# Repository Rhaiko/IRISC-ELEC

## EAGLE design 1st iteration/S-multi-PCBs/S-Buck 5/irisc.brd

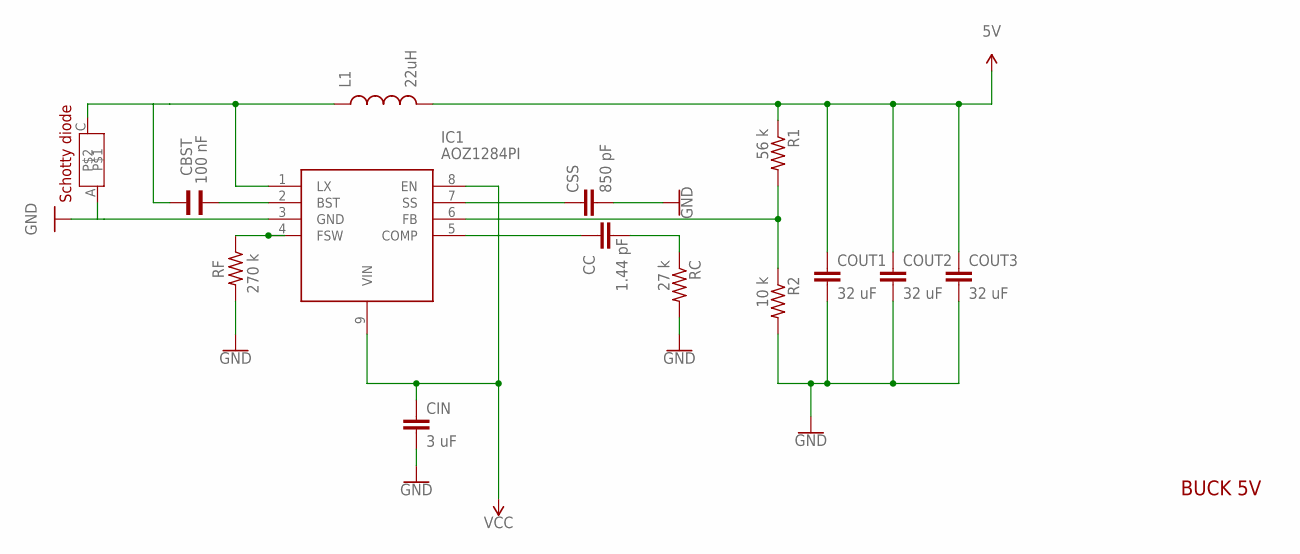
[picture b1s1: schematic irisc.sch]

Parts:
CBST: 100 nF; WCAP-CSGP_0805_WAVE
CC: 1.44 pF; C1206
CIN: 3 uF; C1210
COUT1, COUT2, COUT3: 32 uF; C1812
CSS: 850 pF; C0805
IC1: AOZ1284PI; SOIC127P600X170-9N
L1: 22uH; L0603
R1: 56 k; 0805-THM
R2: 10 k; 0805-THM
RC: 27 k; 0805-THM
RF: 270 k; 0805-THM
U$1: SCHOTTY-DIODE-IRISC; DO-214AC

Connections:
5V: COUT1.1, COUT2.1, COUT3.1, L1.2, R1.1
GND: CIN.2, COUT1.2, COUT2.2, COUT3.2, CSS.2, IC1.3 (GND), R2.2, RC.2, RF.2, U$1.A
unnamed: CSS.1, IC1.7 (SS)
unnamed: IC1.4 (FSW), RF.1
unnamed: CBST.2, IC1.2 (BST)
unnamed: CBST.1, IC1.1 (LX), L1.1, U$1.C
unnamed: CC.1, IC1.5 (COMP)
unnamed: IC1.6 (FB), R1.2, R2.1
unnamed: CC.2, RC.1
VCC: CIN.1, IC1.8 (EN), IC1.9 (VIN)

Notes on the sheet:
BUCK 5V

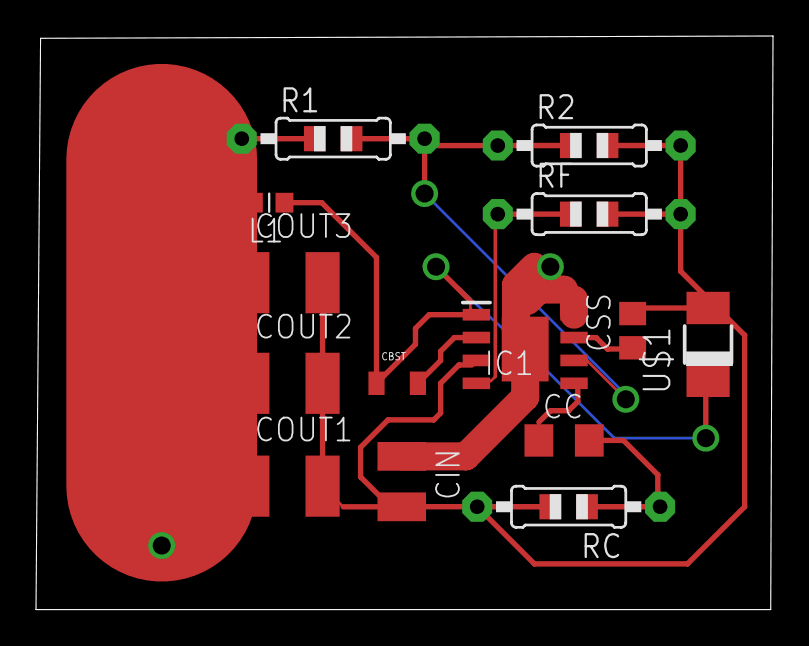
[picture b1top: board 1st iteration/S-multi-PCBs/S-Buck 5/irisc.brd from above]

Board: 2 copper layers, 40.9 x 31.9 mm, 14 parts (0 on the bottom side), 10 nets.

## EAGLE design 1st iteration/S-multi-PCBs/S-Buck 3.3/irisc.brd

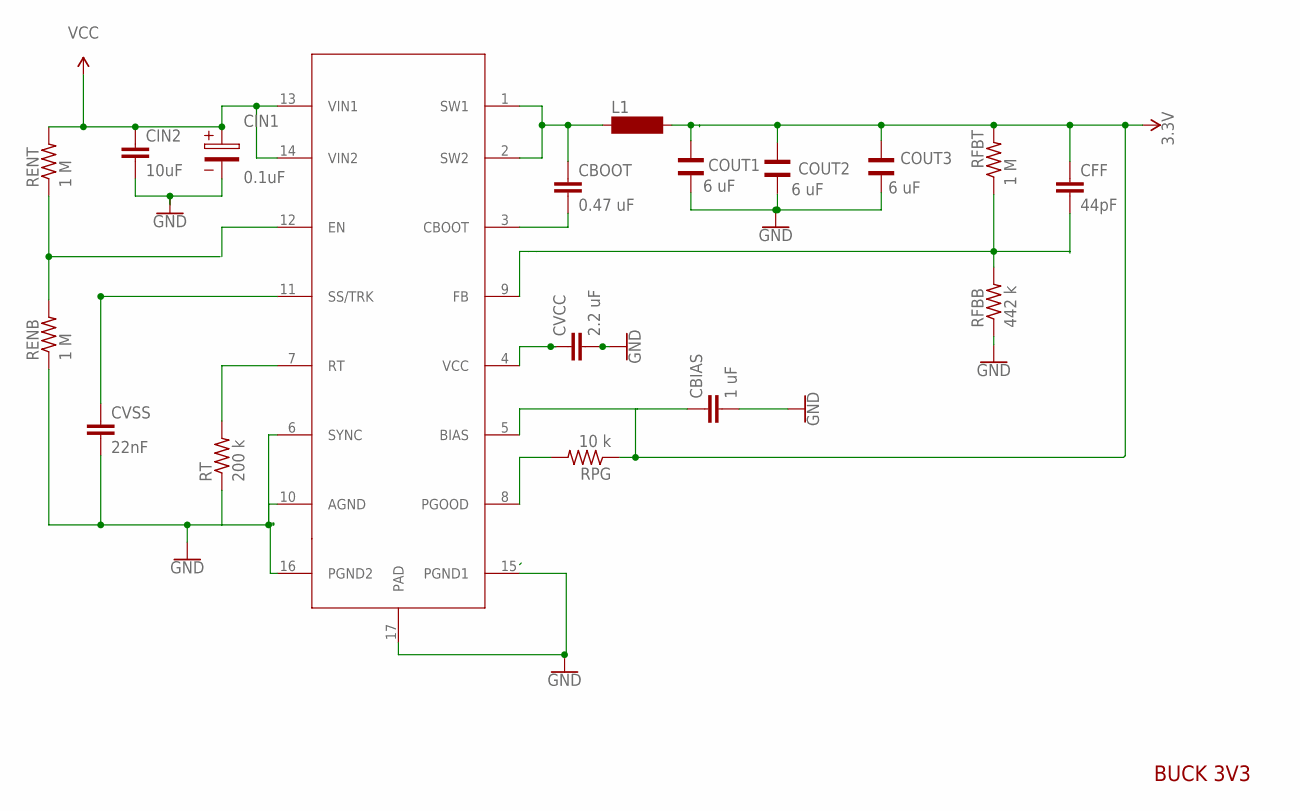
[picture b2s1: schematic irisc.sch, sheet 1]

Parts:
BUCK3V1: BUCK3V3; SOP65P640X120-17N
CBIAS: 1 uF; C1210
CBOOT: 0.47 uF; C1210
CFF: 44pF; C0603
CIN1: 0.1uF; 6.3X2.5X0.9(DXAXB)
CIN2: 10uF; C0805
COUT1, COUT2, COUT3: 6 uF; WCAP-CSGP_0805_WAVE
CVCC: 2.2 uF; C1210
CVSS: 22nF; C1206
L1: BS11
RENB: 1 M; 0805-THM
RENT: 1 M; 0805-THM
RFBB: 442 k; 0805-THM
RFBT: 1 M; 0805-THM
RPG: 10 k; 0805-THM
RT: 200 k; 0805-THM

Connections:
3.3V: BUCK3V1.5 (BIAS), CBIAS.1, CFF.1, COUT1.2, COUT2.2, COUT3.2, L1.2, RFBT.2, RPG.1
GND: CBIAS.2, CIN1.2, CIN2.2, COUT1.1, COUT2.1, COUT3.1, CVCC.2, RFBB.1; also elsewhere on the board
unnamed: BUCK3V1.1 (SW1), BUCK3V1.2 (SW2), CBOOT.1, L1.1
unnamed: BUCK3V1.7 (RT), RT.2
unnamed: BUCK3V1.11 (SS/TRK), CVSS.1
unnamed: BUCK3V1.3 (CBOOT), CBOOT.2
unnamed: CFF.2, RFBB.2, RFBT.1
unnamed: BUCK3V1.4 (VCC), CVCC.1
unnamed: BUCK3V1.8 (PGOOD), RPG.2
unnamed: RENB.2, RENT.1
PGND1: BUCK3V1.15 (PGND1), BUCK3V1.17 (PAD)
PGND2: BUCK3V1.6 (SYNC), BUCK3V1.10 (AGND), BUCK3V1.16 (PGND2), CVSS.2, RENB.1, RT.1
VCC1: BUCK3V1.13 (VIN1), BUCK3V1.14 (VIN2), CIN1.1, CIN2.1, RENT.2

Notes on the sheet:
BUCK 3V3

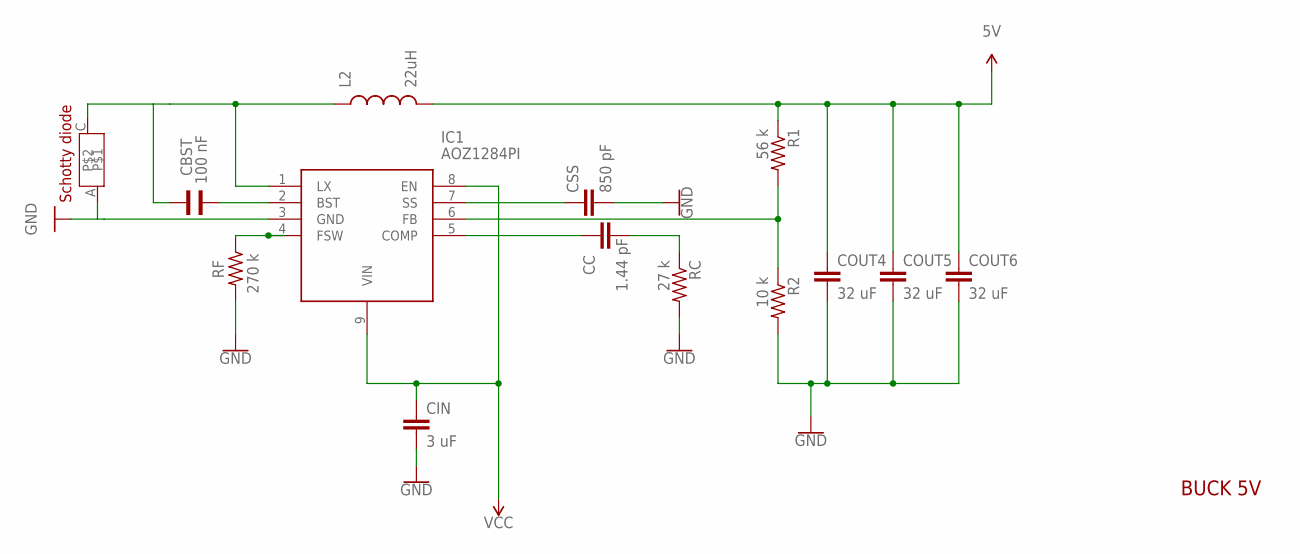
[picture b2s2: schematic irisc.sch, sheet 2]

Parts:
CBST: 100 nF; WCAP-CSGP_0805_WAVE
CC: 1.44 pF; C1206
CIN: 3 uF; C1210
COUT4, COUT5, COUT6: 32 uF; C1812
CSS: 850 pF; C0805
IC1: AOZ1284PI; SOIC127P600X170-9N
L2: 22uH; L0603
R1: 56 k; 0805-THM
R2: 10 k; 0805-THM
RC: 27 k; 0805-THM
RF: 270 k; 0805-THM
U$1: SCHOTTY-DIODE-IRISC; DO-214AC

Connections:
5V: COUT4.1, COUT5.1, COUT6.1, L2.2, R1.1
GND: CIN.2, COUT4.2, COUT5.2, COUT6.2, CSS.2, IC1.3 (GND), R2.2, RC.2, RF.2, U$1.A; also elsewhere on the board
unnamed: IC1.4 (FSW), RF.1
unnamed: CBST.2, IC1.2 (BST)
unnamed: CBST.1, IC1.1 (LX), L2.1, U$1.C
unnamed: CC.1, IC1.5 (COMP)
unnamed: CSS.1, IC1.7 (SS)
unnamed: IC1.6 (FB), R1.2, R2.1
unnamed: CC.2, RC.1
VCC: CIN.1, IC1.8 (EN), IC1.9 (VIN)

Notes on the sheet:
BUCK 5V

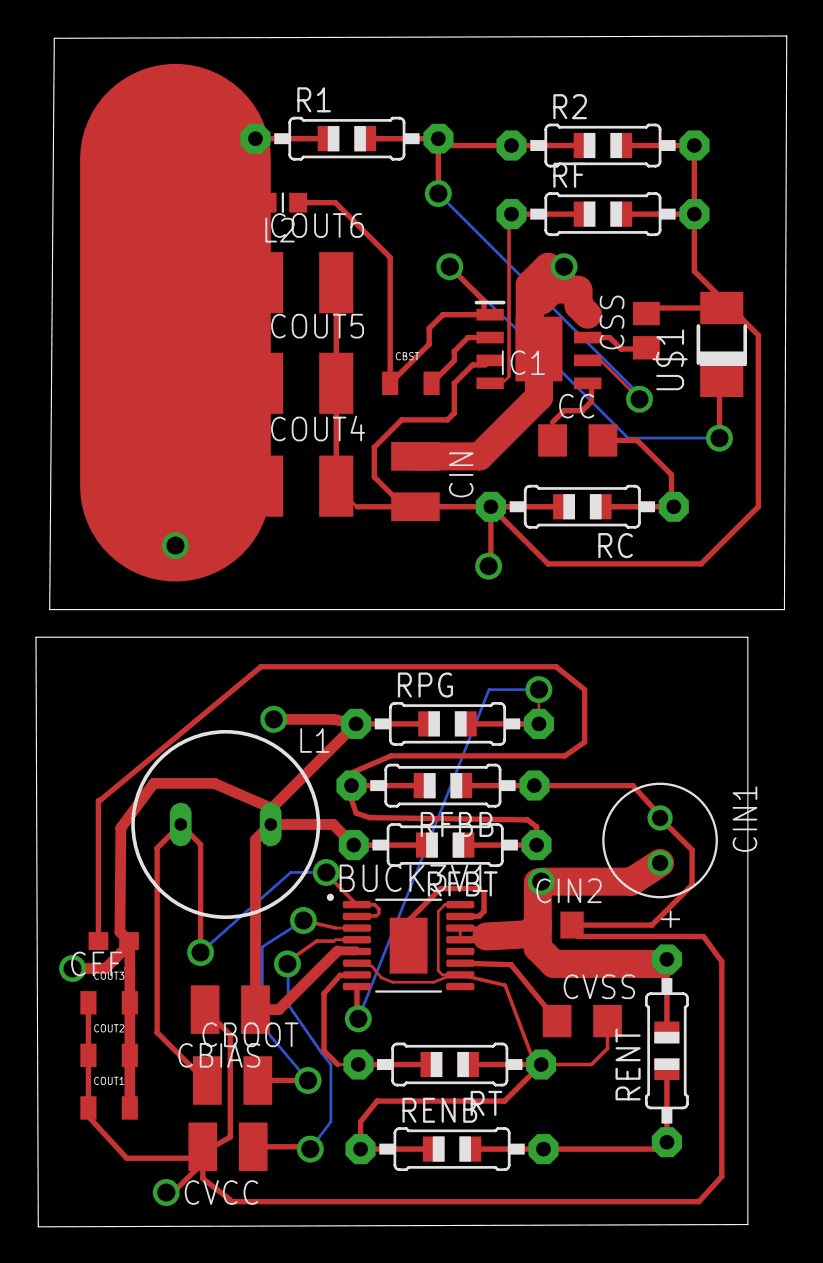
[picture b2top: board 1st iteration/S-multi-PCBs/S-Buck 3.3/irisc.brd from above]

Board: 2 copper layers, 41.7 x 66.2 mm, 32 parts (0 on the bottom side), 22 nets.

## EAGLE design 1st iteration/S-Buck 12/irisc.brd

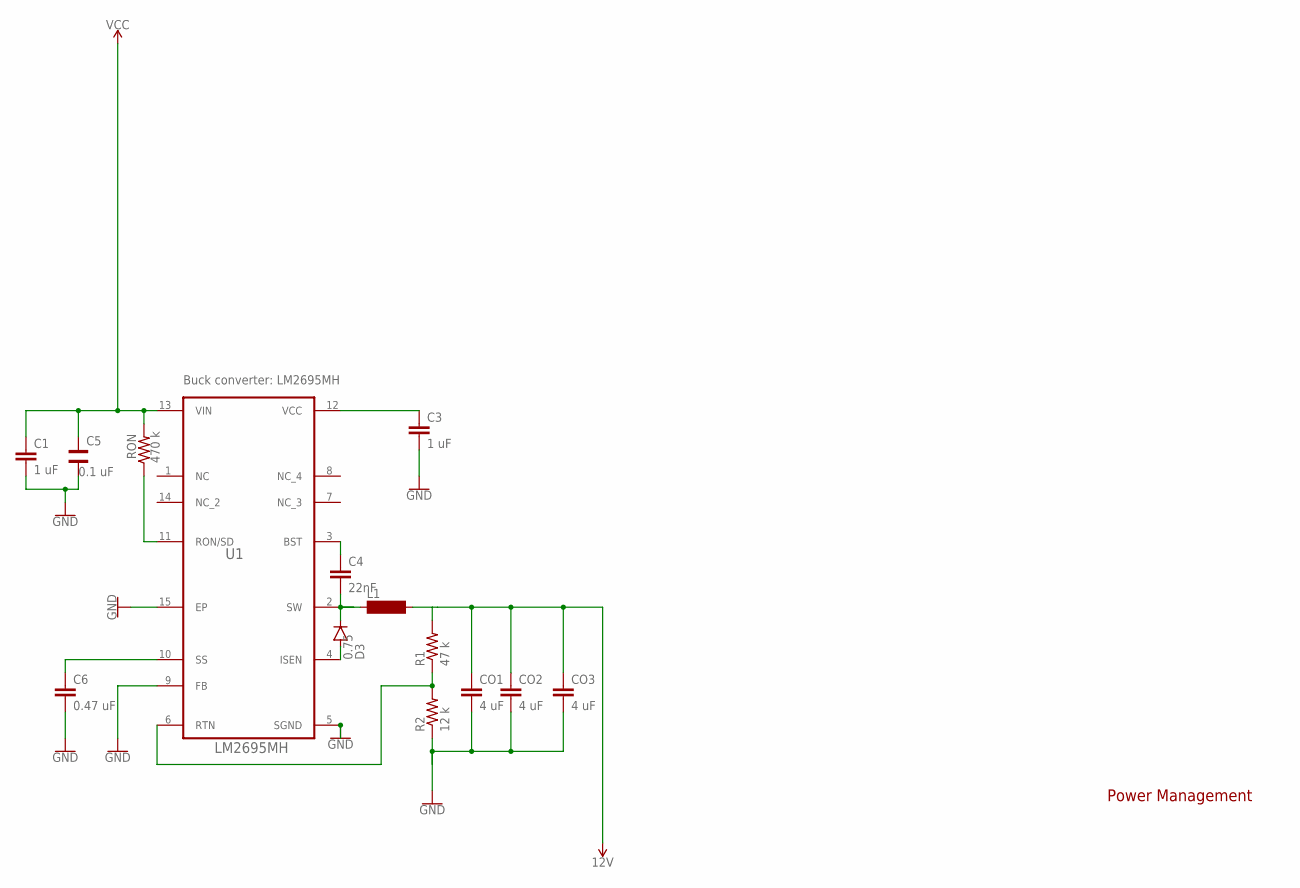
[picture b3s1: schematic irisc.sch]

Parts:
C1, C3: 1 uF; C1210
C4: 22nF; C1206
C5: 0.1 uF; WCAP-CSGP_0805_REFLOW
C6: 0.47 uF; C1210
CO1, CO2, CO3: 4 uF; C1812
D3: 0.75; DIODE-1N4001-KIT
L1: BS11
R1: 47 k; 0805-THM
R2: 12 k; 0805-THM
RON: 470 k; 0805-THM
U1: LM2695MH; SOP65P640X110-15N

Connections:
12V: CO1.1, CO2.1, CO3.1, L1.2, R1.2
GND: C1.2, C3.2, C5.1, C6.2, CO1.2, CO2.2, CO3.2, R2.1, U1.5 (SGND), U1.9 (FB), U1.15 (EP)
unnamed: R1.1, R2.2, U1.6 (RTN)
unnamed: C3.1, U1.12 (VCC)
unnamed: C4.1, U1.3 (BST)
unnamed: C4.2, D3.C, L1.1, U1.2 (SW)
unnamed: RON.1, U1.11 (RON/SD)
unnamed: C6.1, U1.10 (SS)
unnamed: D3.A, U1.4 (ISEN)
VCC: C1.1, C5.2, RON.2, U1.13 (VIN)

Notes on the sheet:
Buck converter: LM2695MH
Power Management

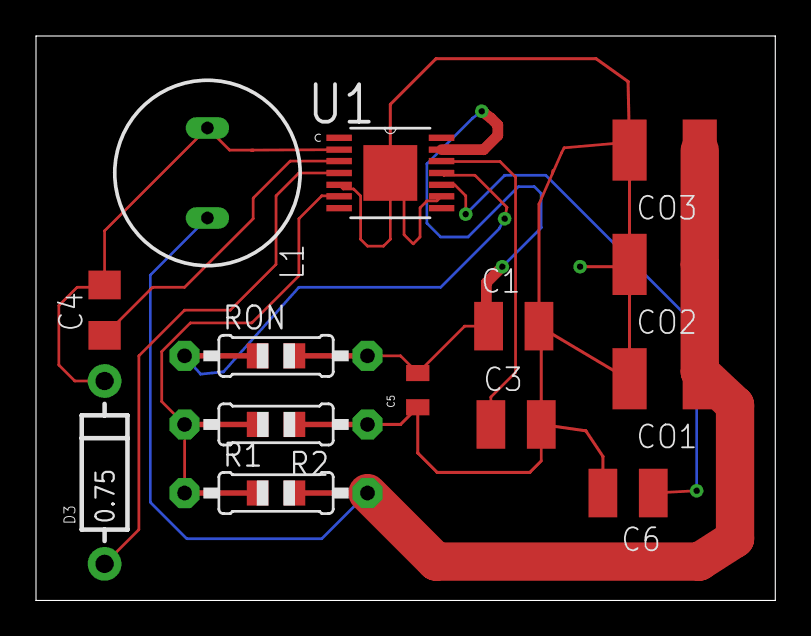
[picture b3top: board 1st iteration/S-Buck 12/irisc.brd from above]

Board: 2 copper layers, 41.1 x 31.4 mm, 14 parts (0 on the bottom side), 10 nets.

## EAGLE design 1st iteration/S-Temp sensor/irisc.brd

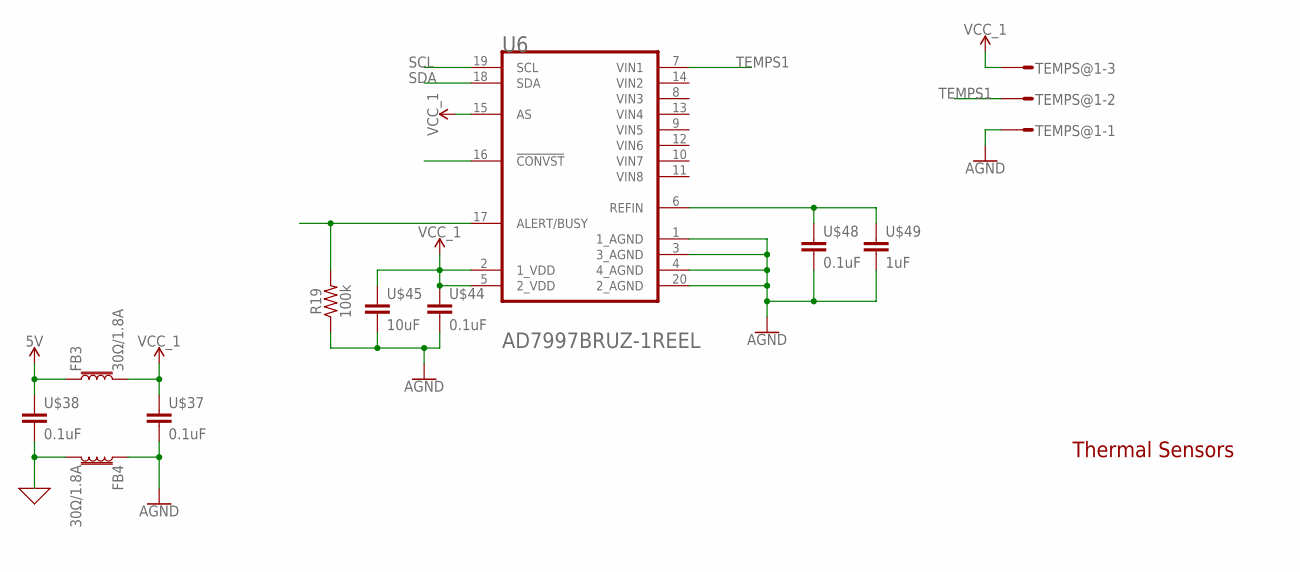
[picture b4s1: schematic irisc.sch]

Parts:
FB3, FB4: 30Ω/1.8A; 0603
R19: 100k; 0603
TEMPS@1: L03P
U6: ANALOG_DEVICES_AD7997BRUZ-1REELANALOG_DEVICES_AD7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; ANALOG_DEVICES_AD7997BRUZ-1REEL_0
U$37, U$38, U$44, U$48: 0.1uF; RESC0603_N
U$45: 10uF; RESC0805_L
U$49: 1uF; RESC0603_N

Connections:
0: FB4.2, U$38.2
5V: FB3.1, U$38.1
AGND: FB4.1, R19.1, TEMPS@1.1, U6.1 (1_AGND), U6.3 (3_AGND), U6.4 (4_AGND), U6.20 (2_AGND), U$37.2, U$44.2, U$45.2, U$48.2, U$49.2
unnamed: U6.6 (REFIN), U$48.1, U$49.1
unnamed: R19.2, U6.17 (ALERT/BUSY)
SCL: U6.19 (SCL)
SDA: U6.18 (SDA)
TEMPS1: TEMPS@1.2, U6.7 (VIN1)
VCC_1: FB3.2, TEMPS@1.3, U6.2 (1_VDD), U6.5 (2_VDD), U6.15 (AS), U$37.1, U$44.1, U$45.1

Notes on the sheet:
Thermal Sensors

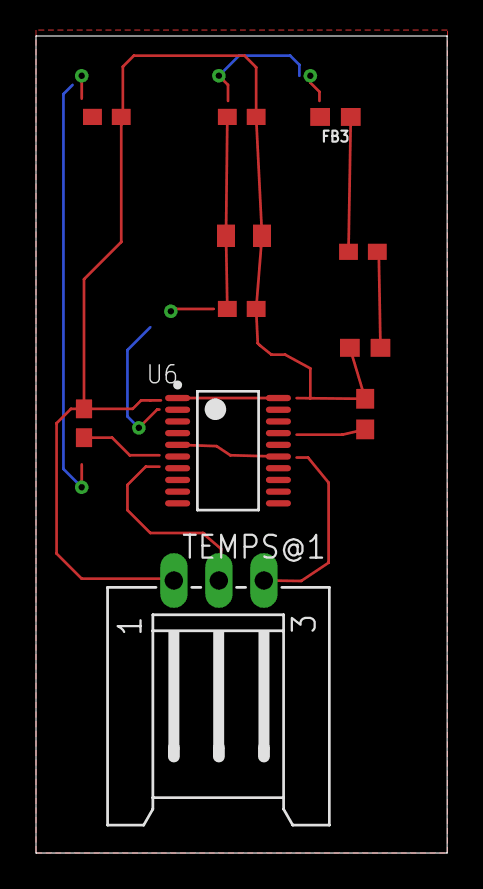
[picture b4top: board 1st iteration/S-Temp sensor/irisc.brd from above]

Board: 2 copper layers, 22.8 x 45.4 mm, 11 parts (0 on the bottom side), 7 nets.

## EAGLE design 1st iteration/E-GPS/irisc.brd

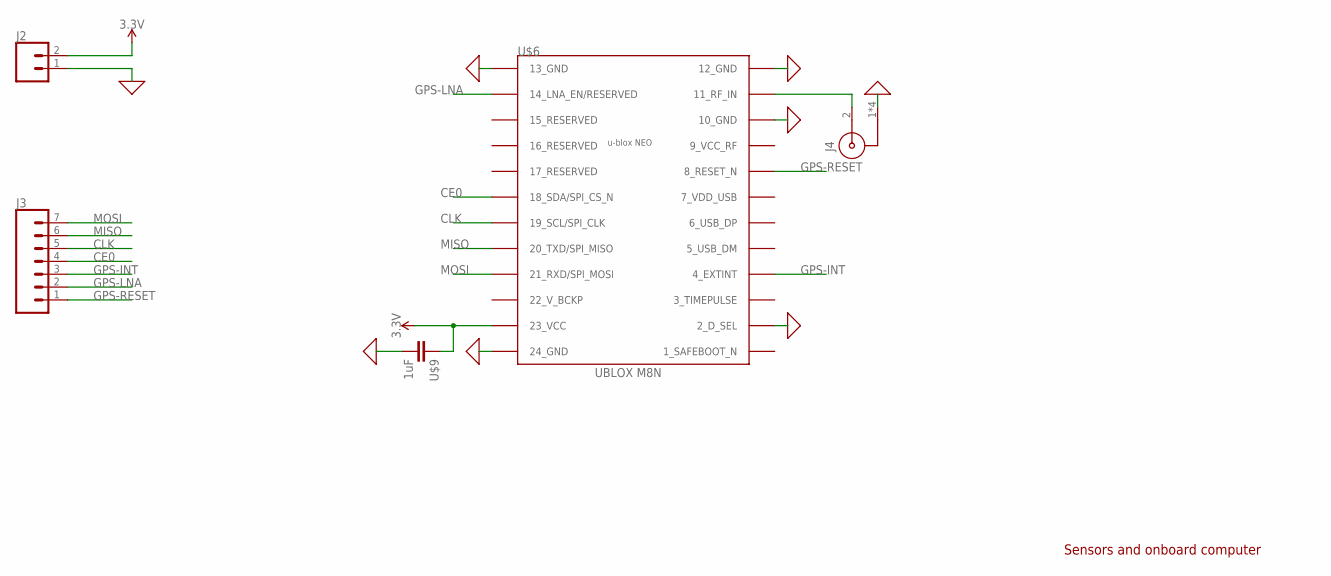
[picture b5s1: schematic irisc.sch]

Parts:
J2: CONN_02; 1X02
J3: CONN_07; 1X07
J4: 60312202114508
U$6: NEO-M8
U$9: 1uF; RESC0603_N

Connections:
0: J2.1, J4.1 (2), J4.3 (2), J4.4 (2), J4.5 (2), U$6.2 (2_D_SEL), U$6.10 (10_GND), U$6.12 (12_GND), U$6.13 (13_GND), U$6.24 (24_GND), U$9.2
3.3V: J2.2, U$6.23 (23_VCC), U$9.1
CE0: J3.4, U$6.18 (18_SDA/SPI_CS_N)
CLK: J3.5, U$6.19 (19_SCL/SPI_CLK)
GPS-INT: J3.3, U$6.4 (4_EXTINT)
GPS-LNA: J3.2, U$6.14 (14_LNA_EN/RESERVED)
GPS-RESET: J3.1, U$6.8 (8_RESET_N)
MISO: J3.6, U$6.20 (20_TXD/SPI_MISO)
MOSI: J3.7, U$6.21 (21_RXD/SPI_MOSI)
unnamed: J4.2 (1), U$6.11 (11_RF_IN)

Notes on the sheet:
Sensors and onboard computer

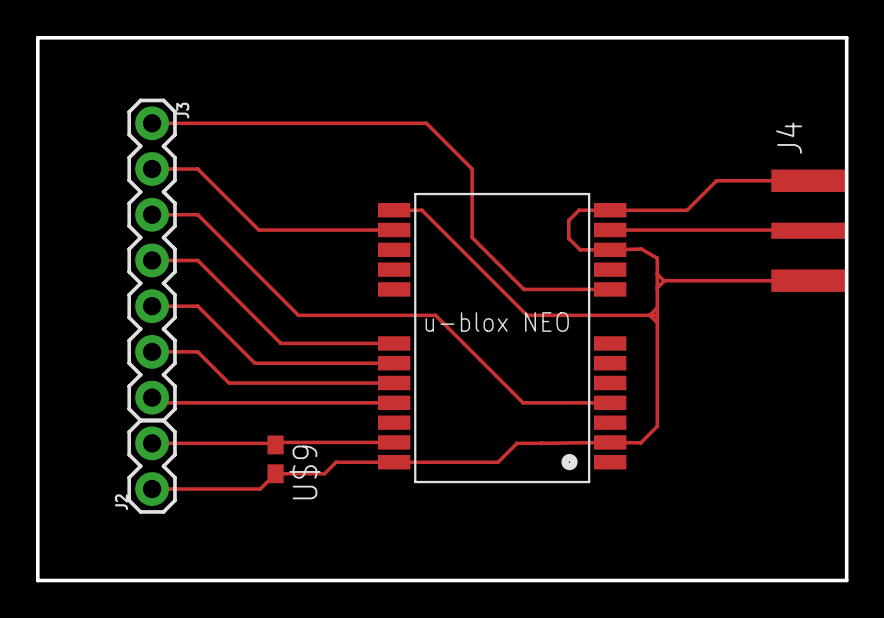
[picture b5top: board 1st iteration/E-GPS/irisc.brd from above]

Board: 2 copper layers, 44.9 x 30.1 mm, 5 parts (0 on the bottom side), 10 nets.

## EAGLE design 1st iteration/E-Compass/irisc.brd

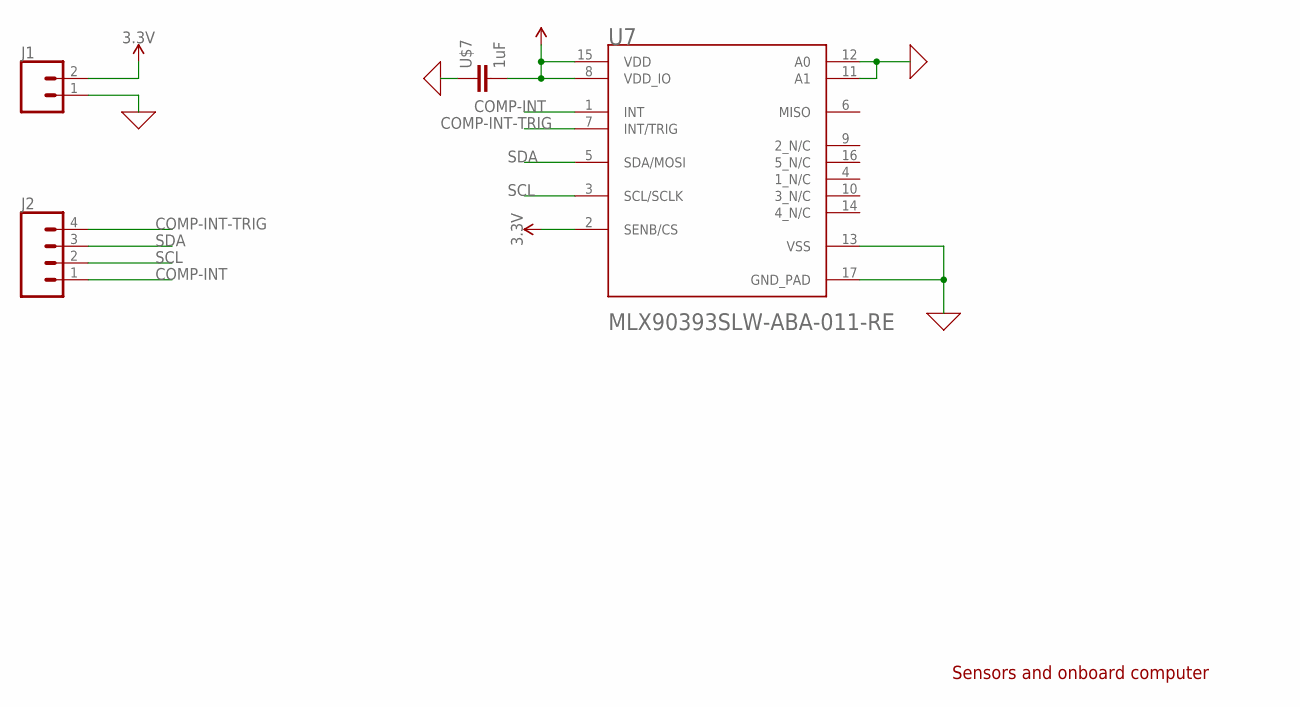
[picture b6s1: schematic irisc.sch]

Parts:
J1: CONN_02; 1X02
J2: CONN_04; 1X04
U7: MELEXIS_TECHNOLOGIES_MLX90393SLW-ABA-011-REMELEXI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; MELEXIS_TECHNOLOGIES_MLX90393SLW-ABA-011-RE_0
U$7: 1uF; RESC0603_N

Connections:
0: J1.1, U7.11 (A1), U7.12 (A0), U7.13 (VSS), U7.17 (GND_PAD), U$7.1
3.3V: J1.2, U7.2 (SENB/CS), U7.8 (VDD_IO), U7.15 (VDD), U$7.2
COMP-INT: J2.1, U7.1 (INT)
COMP-INT-TRIG: J2.4, U7.7 (INT/TRIG)
SCL: J2.2, U7.3 (SCL/SCLK)
SDA: J2.3, U7.5 (SDA/MOSI)

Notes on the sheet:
Sensors and onboard computer

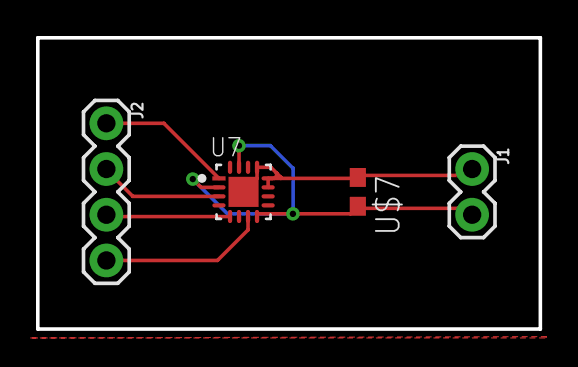
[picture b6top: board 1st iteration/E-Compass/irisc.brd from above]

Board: 2 copper layers, 27.9 x 16.2 mm, 4 parts (0 on the bottom side), 6 nets.

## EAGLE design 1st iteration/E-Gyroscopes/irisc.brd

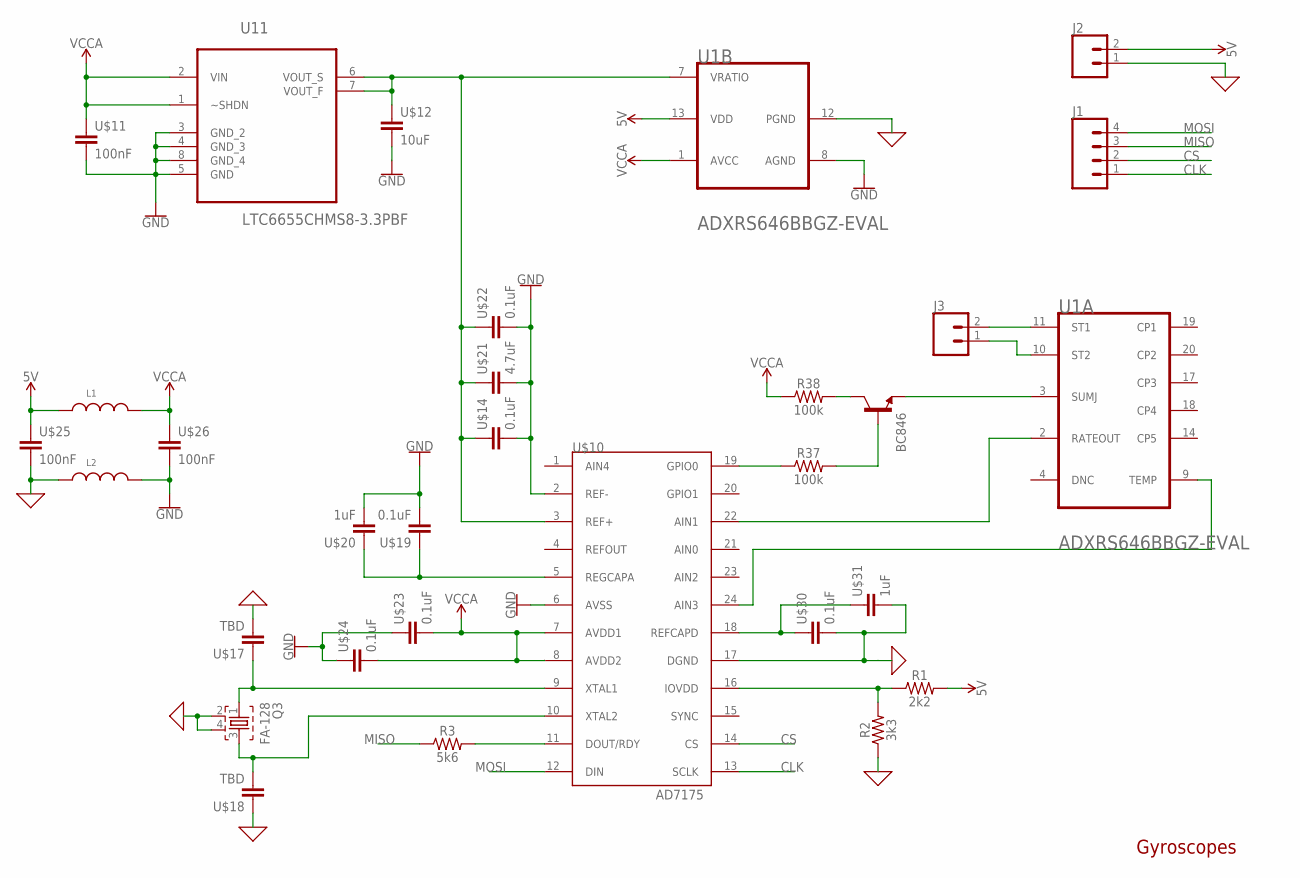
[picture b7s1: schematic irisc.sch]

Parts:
J1: CONN_04; 1X04
J2, J3: CONN_02; 1X02
L1, L2: WE-CBA_0805_782853152_HC; WE-CBA_0805(W=4)
Q3: FA-128
R1: 2k2; AXIAL-0.3-KIT
R2: 3k3; AXIAL-0.3-KIT
R3: 5k6; AXIAL-0.3-KIT
R37, R38: 100k; AXIAL-0.3-KIT
T1: BC846; SOT23
U1: ANALOG_DEVICES_ADXRS646BBGZEVAL; HDRVR20W64P762X254_2X10_2540X1016X254B
U11: LTC6655CHMS8-3.3PBF; SOP65P490X110-8N
U$10: AD7175; TSSOP24
U$11, U$25, U$26: 100nF; RESC0603_N
U$12: 10uF; RESC0805_L
U$14, U$19, U$22, U$23, U$24, U$30: 0.1uF; RESC0603_N
U$17, U$18: TBD; RESC0805_L
U$20, U$31: 1uF; RESC0603_N
U$21: 4.7uF; RESC0603_N

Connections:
0: J2.1, L2.1, Q3.2, Q3.4, R2.P$1 (1), U1.12 (PGND), U$10.17 (DGND), U$17.2, U$18.1, U$25.2, U$30.2, U$31.2
5V: J2.2, L1.1, R1.P$2 (2), U1.13 (VDD), U$25.1
CLK: J1.1, U$10.13 (SCLK)
CP5: U1.14 (CP5)
CS: J1.2, U$10.14 (CS)
GND: L2.2, U1.8 (AGND), U11.3 (GND_2), U11.4 (GND_3), U11.5 (GND), U11.8 (GND_4), U$10.2 (REF-), U$10.6 (AVSS), U$11.2, U$12.2, U$14.2, U$19.2, U$20.2, U$21.2, U$22.2, U$23.1, U$24.1, U$26.2
MISO: J1.3, R3.P$1 (1)
MOSI: J1.4, U$10.12 (DIN)
unnamed: J3.1, U1.10 (ST2)
unnamed: Q3.3, U$10.10 (XTAL2), U$18.2
unnamed: Q3.1, U$10.9 (XTAL1), U$17.1
unnamed: J3.2, U1.11 (ST1)
unnamed: R38.P$2 (2), T1.3 (C)
unnamed: U$10.5 (REGCAPA), U$19.1, U$20.1
unnamed: R37.P$2 (2), T1.1 (B)
unnamed: U1.7 (VRATIO), U11.6 (VOUT_S), U11.7 (VOUT_F), U$10.3 (REF+), U$12.1, U$14.1, U$21.1, U$22.1
unnamed: R1.P$1 (1), R2.P$2 (2), U$10.16 (IOVDD)
unnamed: U$10.18 (REFCAPD), U$30.1, U$31.1
unnamed: T1.2 (E), U1.3 (SUMJ)
unnamed: U1.2 (RATEOUT), U$10.22 (AIN1)
unnamed: U1.9 (TEMP), U$10.24 (AIN3)
unnamed: R37.P$1 (1), U$10.19 (GPIO0)
SDF: R3.P$2 (2), U$10.11 (DOUT/RDY)
VCCA: L1.2, R38.P$1 (1), U1.1 (AVCC), U11.1 (~SHDN), U11.2 (VIN), U$10.7 (AVDD1), U$10.8 (AVDD2), U$11.1, U$23.2, U$24.2, U$26.1

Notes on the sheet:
Gyroscopes

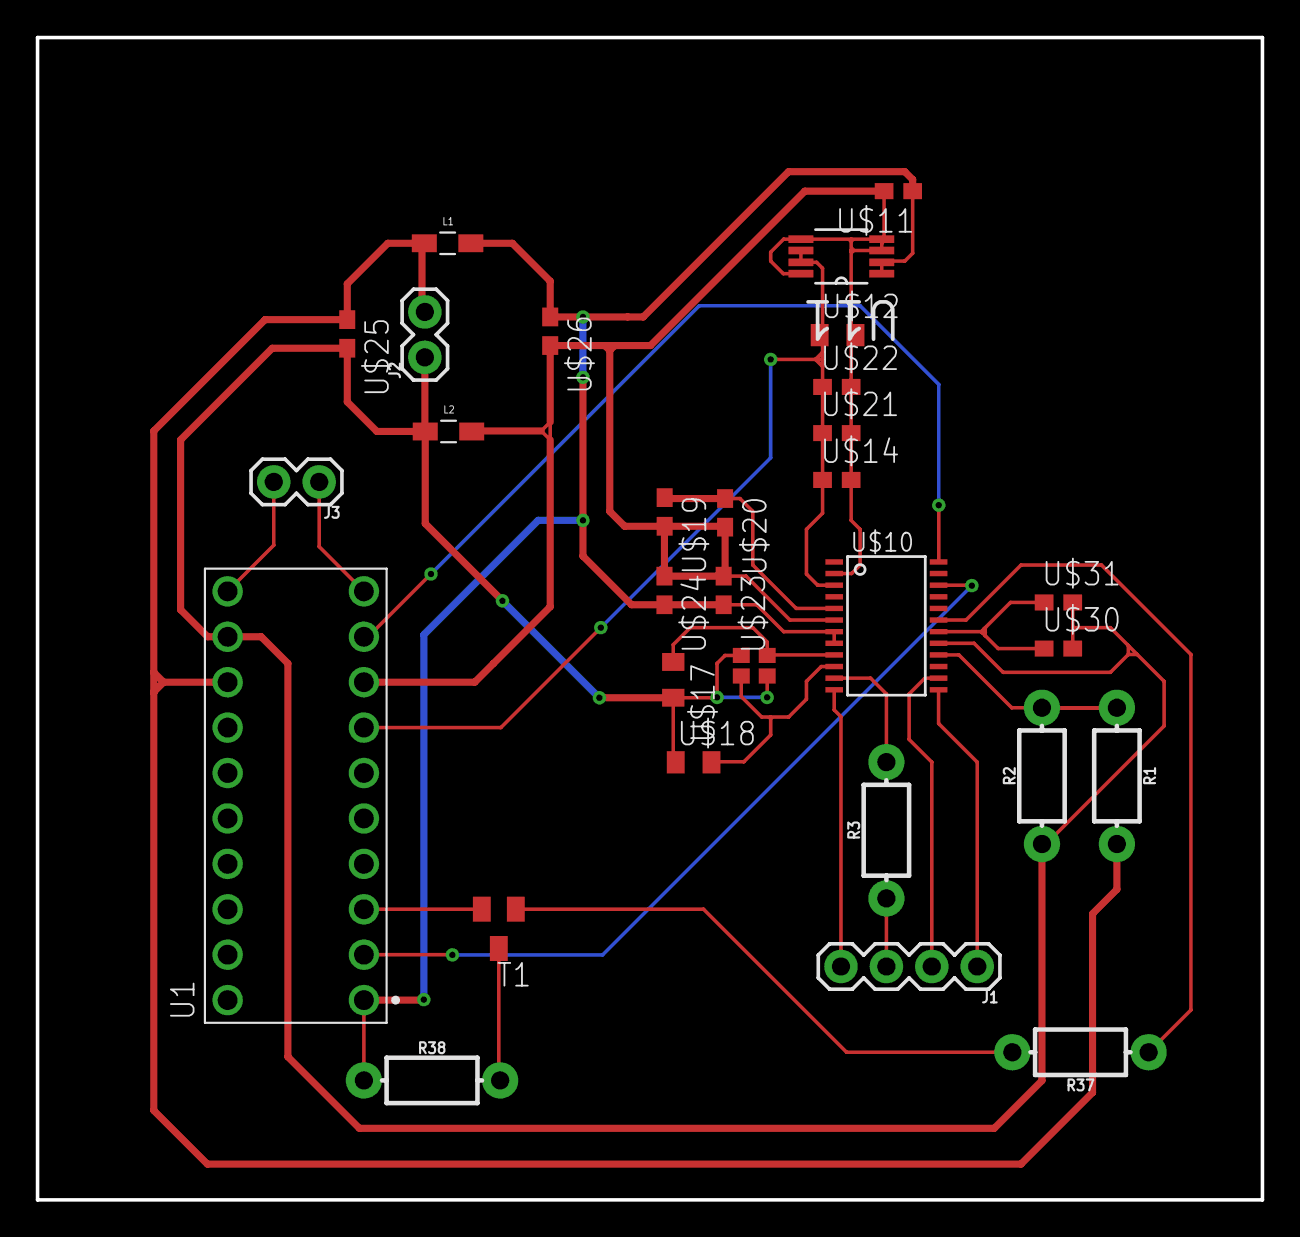
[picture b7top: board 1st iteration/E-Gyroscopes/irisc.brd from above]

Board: 2 copper layers, 68.5 x 65.0 mm, 30 parts (0 on the bottom side), 23 nets.

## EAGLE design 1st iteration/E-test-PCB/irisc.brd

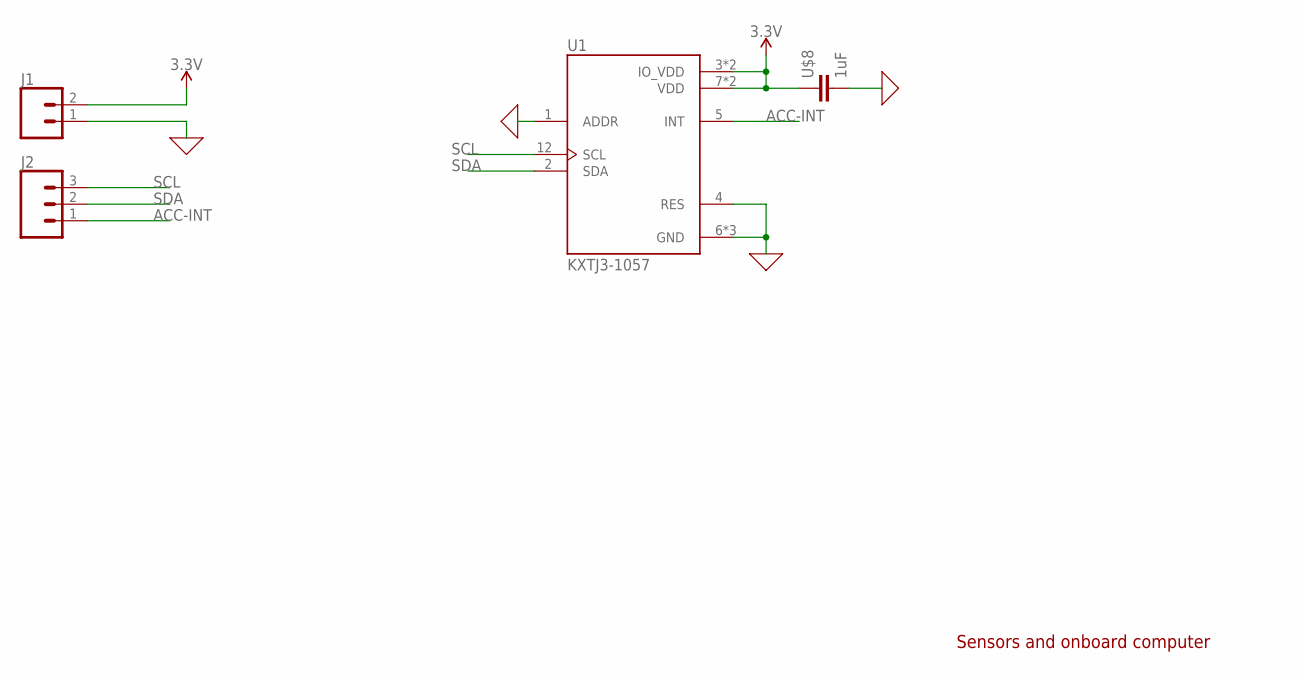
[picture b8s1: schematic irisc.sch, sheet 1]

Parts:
J1: CONN_02; 1X02
J2: CONN_03; 1X03
U1: KXTJ3-1057; KIONIX_KXTJ3-1057
U$8: 1uF; RESC0603_N

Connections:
0: J1.1, U1.1 (ADDR), U1.4 (RES), U1.6 (GND), U1.8 (GND), U1.9 (GND), U$8.2; also elsewhere on the board
3.3V: J1.2, U1.3 (IO_VDD), U1.7 (VDD), U1.10 (VDD), U1.11 (IO_VDD), U$8.1; also elsewhere on the board
ACC-INT: J2.1, U1.5 (INT)
SCL: J2.3, U1.12 (SCL); also elsewhere on the board
SDA: J2.2, U1.2 (SDA); also elsewhere on the board

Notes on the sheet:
Sensors and onboard computer

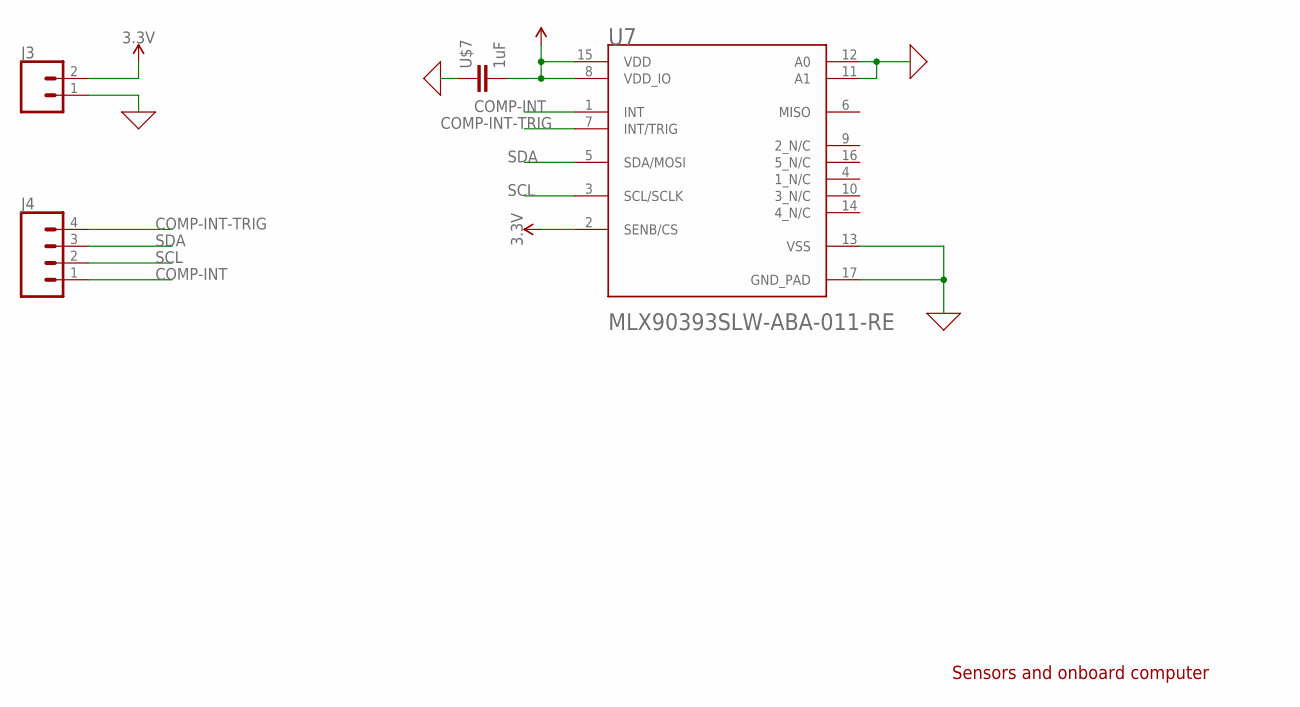
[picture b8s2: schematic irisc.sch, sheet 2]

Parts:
J3: CONN_02; 1X02
J4: CONN_04; 1X04
U7: MELEXIS_TECHNOLOGIES_MLX90393SLW-ABA-011-REMELEXI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; MELEXIS_TECHNOLOGIES_MLX90393SLW-ABA-011-RE_0
U$7: 1uF; RESC0603_N

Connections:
0: J3.1, U7.11 (A1), U7.12 (A0), U7.13 (VSS), U7.17 (GND_PAD), U$7.1; also elsewhere on the board
3.3V: J3.2, U7.2 (SENB/CS), U7.8 (VDD_IO), U7.15 (VDD), U$7.2; also elsewhere on the board
COMP-INT: J4.1, U7.1 (INT)
COMP-INT-TRIG: J4.4, U7.7 (INT/TRIG)
SCL: J4.2, U7.3 (SCL/SCLK); also elsewhere on the board
SDA: J4.3, U7.5 (SDA/MOSI); also elsewhere on the board

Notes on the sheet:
Sensors and onboard computer

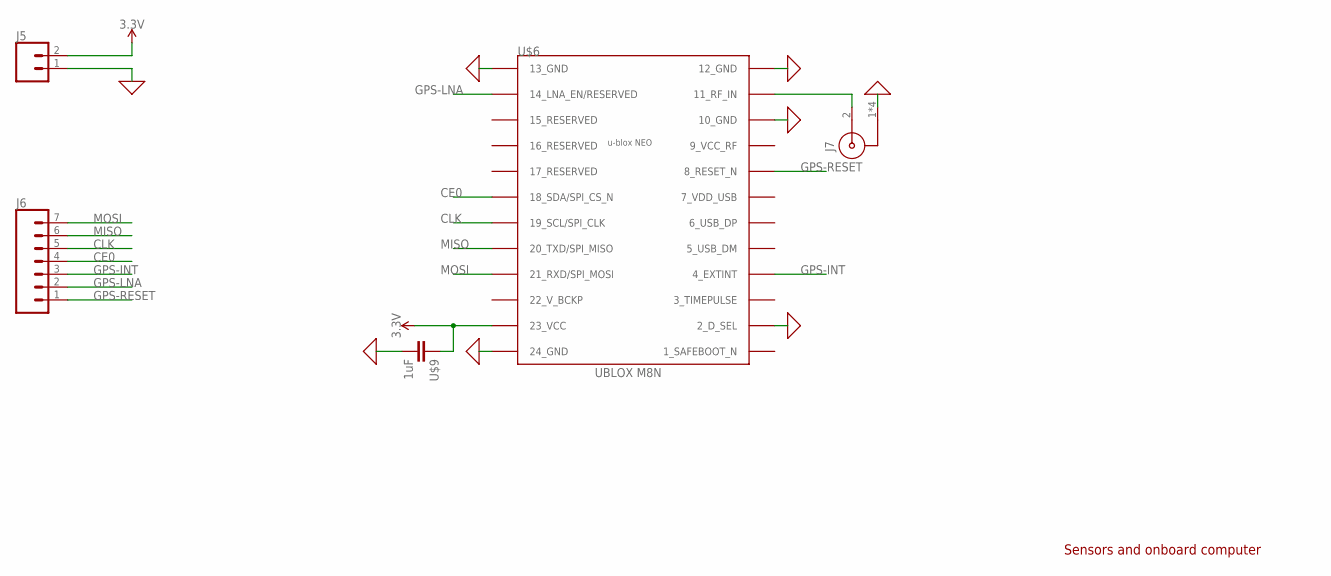
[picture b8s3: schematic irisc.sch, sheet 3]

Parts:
J5: CONN_02; 1X02
J6: CONN_07; 1X07
J7: 60312202114508
U$6: NEO-M8
U$9: 1uF; RESC0603_N

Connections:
0: J5.1, J7.1 (2), J7.3 (2), J7.4 (2), J7.5 (2), U$6.2 (2_D_SEL), U$6.10 (10_GND), U$6.12 (12_GND), U$6.13 (13_GND), U$6.24 (24_GND), U$9.2; also elsewhere on the board
3.3V: J5.2, U$6.23 (23_VCC), U$9.1; also elsewhere on the board
CE0: J6.4, U$6.18 (18_SDA/SPI_CS_N)
CLK: J6.5, U$6.19 (19_SCL/SPI_CLK); also elsewhere on the board
GPS-INT: J6.3, U$6.4 (4_EXTINT)
GPS-LNA: J6.2, U$6.14 (14_LNA_EN/RESERVED)
GPS-RESET: J6.1, U$6.8 (8_RESET_N)
MISO: J6.6, U$6.20 (20_TXD/SPI_MISO); also elsewhere on the board
MOSI: J6.7, U$6.21 (21_RXD/SPI_MOSI); also elsewhere on the board
unnamed: J7.2 (1), U$6.11 (11_RF_IN)

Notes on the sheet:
Sensors and onboard computer

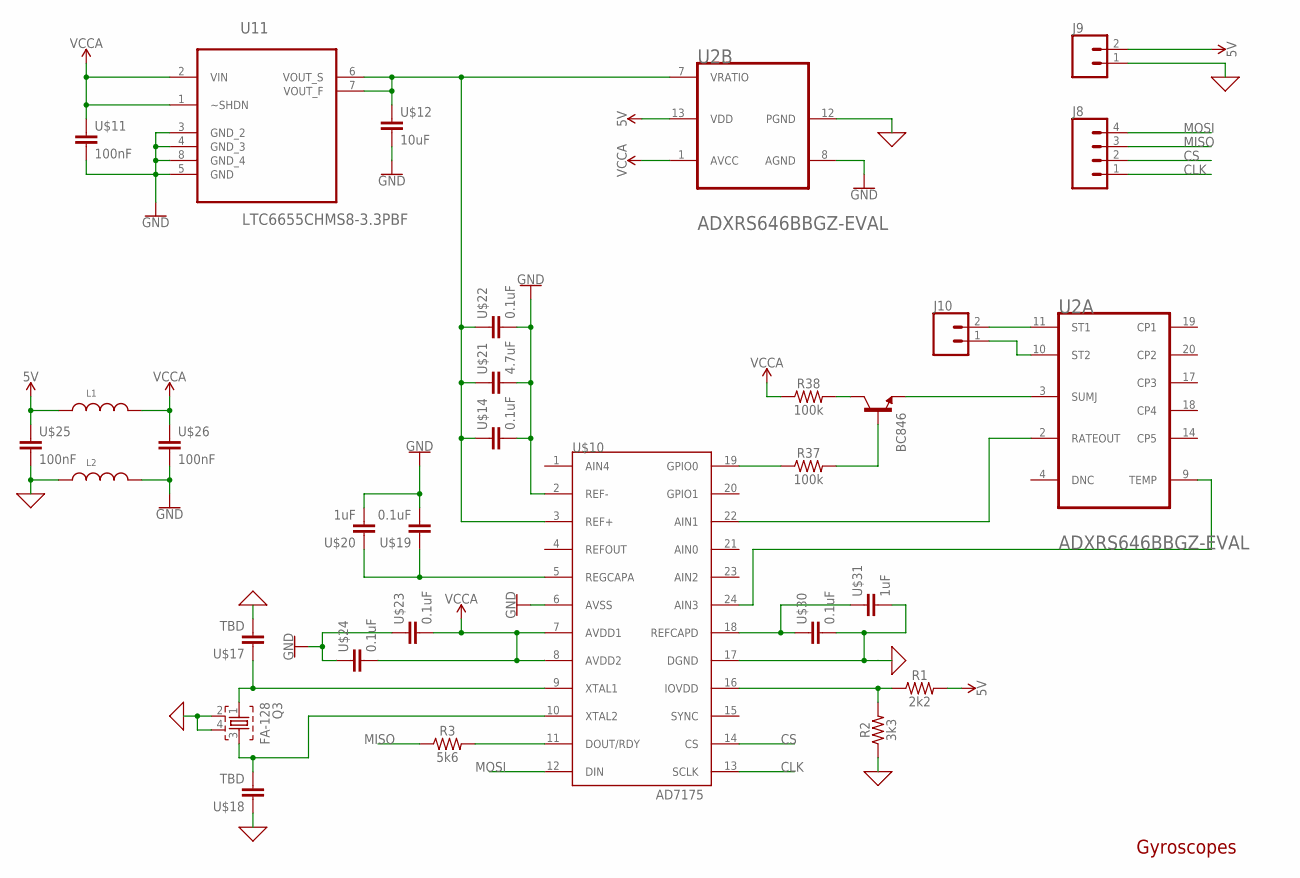
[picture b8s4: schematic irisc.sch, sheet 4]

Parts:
J8: CONN_04; 1X04
J9, J10: CONN_02; 1X02
L1, L2: WE-CBA_0805_782853152_HC; WE-CBA_0805(W=4)
Q3: FA-128
R1: 2k2; AXIAL-0.3-KIT
R2: 3k3; AXIAL-0.3-KIT
R3: 5k6; AXIAL-0.3-KIT
R37, R38: 100k; AXIAL-0.3-KIT
T1: BC846; SOT23
U2: ANALOG_DEVICES_ADXRS646BBGZEVAL; HDRVR20W64P762X254_2X10_2540X1016X254B
U11: LTC6655CHMS8-3.3PBF; SOP65P490X110-8N
U$10: AD7175; TSSOP24
U$11, U$25, U$26: 100nF; RESC0603_N
U$12: 10uF; RESC0805_L
U$14, U$19, U$22, U$23, U$24, U$30: 0.1uF; RESC0603_N
U$17, U$18: TBD; RESC0805_L
U$20, U$31: 1uF; RESC0603_N
U$21: 4.7uF; RESC0603_N

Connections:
0: J9.1, L2.1, Q3.2, Q3.4, R2.P$1 (1), U2.12 (PGND), U$10.17 (DGND), U$17.2, U$18.1, U$25.2, U$30.2, U$31.2; also elsewhere on the board
5V: J9.2, L1.1, R1.P$2 (2), U2.13 (VDD), U$25.1; also elsewhere on the board
CLK: J8.1, U$10.13 (SCLK); also elsewhere on the board
CP5: U2.14 (CP5)
CS: J8.2, U$10.14 (CS)
GND: L2.2, U2.8 (AGND), U11.3 (GND_2), U11.4 (GND_3), U11.5 (GND), U11.8 (GND_4), U$10.2 (REF-), U$10.6 (AVSS), U$11.2, U$12.2, U$14.2, U$19.2, U$20.2, U$21.2, U$22.2, U$23.1, U$24.1, U$26.2
MISO: J8.3, R3.P$1 (1); also elsewhere on the board
MOSI: J8.4, U$10.12 (DIN); also elsewhere on the board
unnamed: J10.1, U2.10 (ST2)
unnamed: Q3.3, U$10.10 (XTAL2), U$18.2
unnamed: Q3.1, U$10.9 (XTAL1), U$17.1
unnamed: J10.2, U2.11 (ST1)
unnamed: R38.P$2 (2), T1.3 (C)
unnamed: U$10.5 (REGCAPA), U$19.1, U$20.1
unnamed: R37.P$2 (2), T1.1 (B)
unnamed: U2.7 (VRATIO), U11.6 (VOUT_S), U11.7 (VOUT_F), U$10.3 (REF+), U$12.1, U$14.1, U$21.1, U$22.1
unnamed: R1.P$1 (1), R2.P$2 (2), U$10.16 (IOVDD)
unnamed: U$10.18 (REFCAPD), U$30.1, U$31.1
unnamed: T1.2 (E), U2.3 (SUMJ)
unnamed: U2.2 (RATEOUT), U$10.22 (AIN1)
unnamed: U2.9 (TEMP), U$10.24 (AIN3)
unnamed: R37.P$1 (1), U$10.19 (GPIO0)
SDF: R3.P$2 (2), U$10.11 (DOUT/RDY)
VCCA: L1.2, R38.P$1 (1), U2.1 (AVCC), U11.1 (~SHDN), U11.2 (VIN), U$10.7 (AVDD1), U$10.8 (AVDD2), U$11.1, U$23.2, U$24.2, U$26.1

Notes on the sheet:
Gyroscopes

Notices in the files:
parts and their libraries:
SparkFun-PowerSymbols: Licensing: Creative Commons ShareAlike 4.0 International - https://creativecommons.org/licenses/by-sa/4.0
Wurth_Elektronik_Electromechanic_Coaxial: Copyright: Würth Elektronik
